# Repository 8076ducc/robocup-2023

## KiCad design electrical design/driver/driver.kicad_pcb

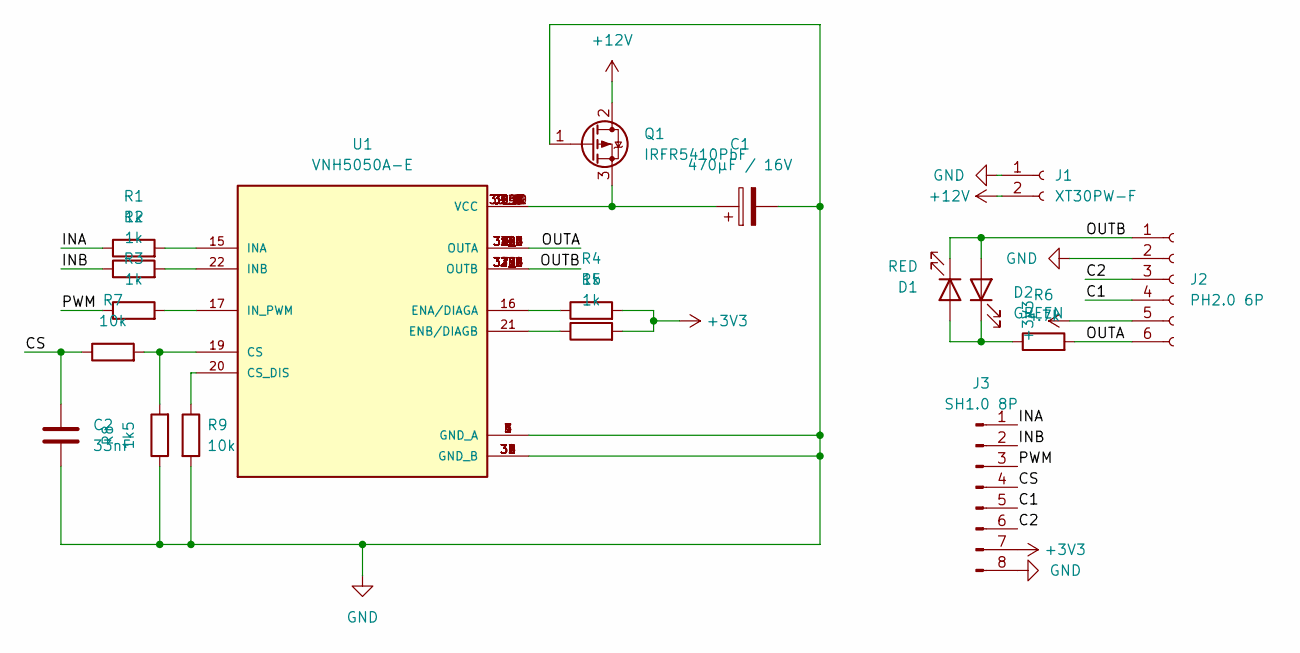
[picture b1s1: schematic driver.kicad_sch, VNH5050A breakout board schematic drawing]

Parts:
C1: 470µF / 16V; CP_Elec_8x10.5
C2: 33nF; C_0603_1608Metric
D1: RED; D_0603_1608Metric
D2: GREEN; D_0603_1608Metric
J1: XT30PW-F; AMASS_XT30PW-F_1x02_P2.50mm_Horizontal
J2: PH2.0 6P; JST_PH_S6B-PH-K_1x06_P2.00mm_Horizontal
J3: SH1.0 8P; JST_SH_BM08B-SRSS-TB_1x08-1MP_P1.00mm_Vertical
Q1: IRFR5410PbF; TO-252-2
R1, R2, R3, R4, R5: 1k; R_0603_1608Metric
R6: 4.7k; R_0603_1608Metric
R7, R9: 10k; R_0603_1608Metric
R8: 1k5; R_0603_1608Metric
U1: VNH5050A-E; SOP50P1030X247-39N; PARTREV 1.0

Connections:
+3V3: J2.5, J3.7, R4.2, R5.2
+12V: J1.2, Q1.2 (D)
/C1: J2.4, J3.5
/C2: J2.3, J3.6
/CS: C2.1, J3.4, R7.1
/INA: J3.1, R1.1
/INB: J3.2, R2.1
/OUTA: J2.6, R6.2, U1.2 (OUTA), U1.8 (OUTA), U1.9 (OUTA), U1.10 (OUTA), U1.11 (OUTA), U1.12 (OUTA), U1.14 (OUTA), U1.38 (OUTA), U1.38_1 (OUTA), U1.38_2 (OUTA), U1.38_3 (OUTA), U1.38_4 (OUTA), U1.38_5 (OUTA), U1.38_6 (OUTA)
/OUTB: D1.1 (K), D2.2 (A), J2.1, U1.23 (OUTB), U1.25 (OUTB), U1.26 (OUTB), U1.27 (OUTB), U1.28 (OUTB), U1.29 (OUTB), U1.35 (OUTB), U1.37 (OUTB), U1.37_1 (OUTB), U1.37_2 (OUTB), U1.37_3 (OUTB), U1.37_4 (OUTB), U1.37_5 (OUTB), U1.37_6 (OUTB)
/PWM: J3.3, R3.1
GND: C1.2, C2.2, J1.1, J2.2, J3.8, Q1.1 (G), R8.1, R9.2, U1.1 (GND_A), U1.3 (GND_A), U1.4 (GND_A), U1.5 (GND_A), U1.6 (GND_A), U1.7 (GND_A), U1.30 (GND_B), U1.31 (GND_B), U1.32 (GND_B), U1.33 (GND_B), U1.34 (GND_B), U1.36 (GND_B)
unnamed: C1.1, Q1.3 (S), U1.13 (VCC), U1.24 (VCC), U1.39 (VCC), U1.39_1 (VCC), U1.39_2 (VCC), U1.39_3 (VCC), U1.39_4 (VCC), U1.39_5 (VCC), U1.39_6 (VCC), U1.39_7 (VCC), U1.39_8 (VCC), U1.39_9 (VCC), U1.39_10 (VCC), U1.39_11 (VCC), U1.39_12 (VCC)
unnamed: D1.2 (A), D2.1 (K), R6.1
unnamed: R1.2, U1.15 (INA)
unnamed: R2.2, U1.22 (INB)
unnamed: R3.2, U1.17 (IN_PWM)
unnamed: R4.1, U1.16 (ENA/DIAGA)
unnamed: R5.1, U1.21 (ENB/DIAGB)
unnamed: R7.2, R8.2, U1.19 (CS)
unnamed: R9.1, U1.20 (CS_DIS)

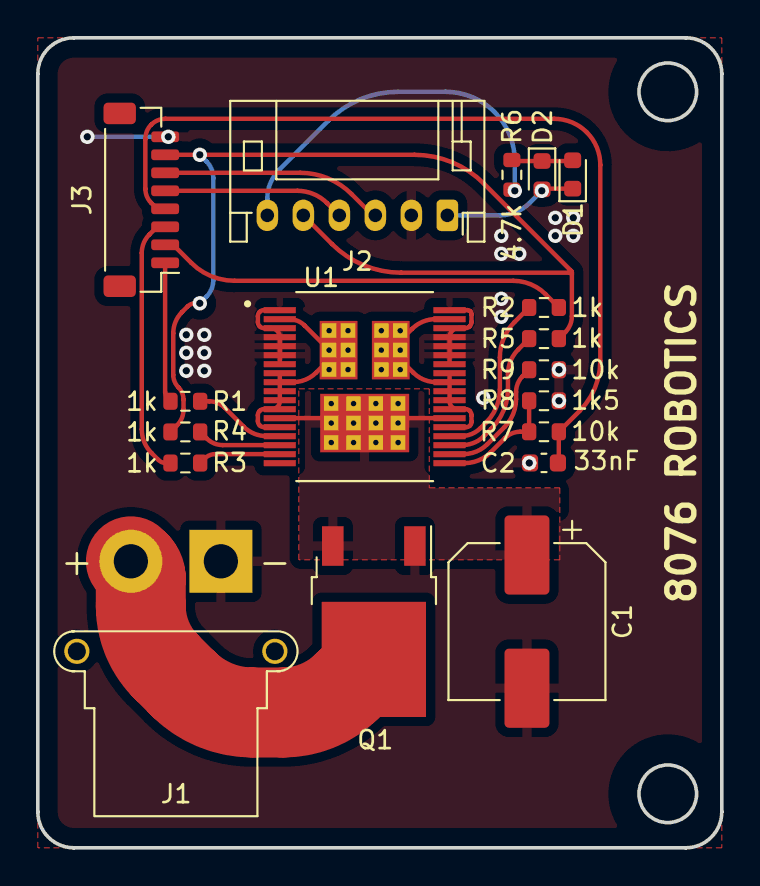
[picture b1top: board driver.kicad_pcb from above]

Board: 2 copper layers, 38.0 x 45.0 mm, 18 parts (0 on the bottom side), 20 nets.

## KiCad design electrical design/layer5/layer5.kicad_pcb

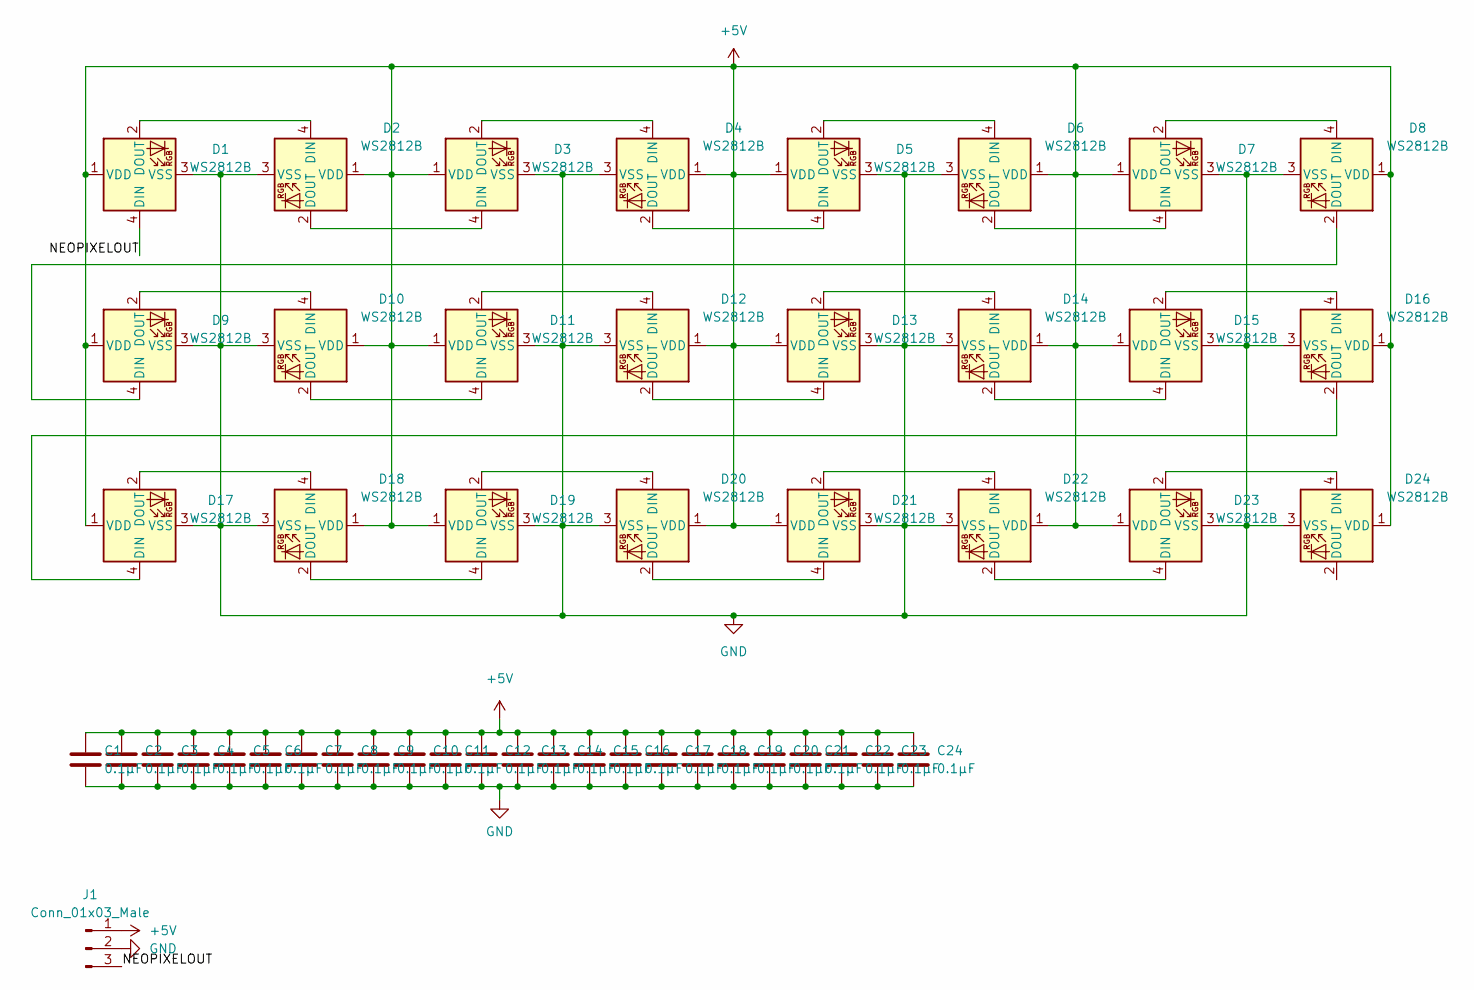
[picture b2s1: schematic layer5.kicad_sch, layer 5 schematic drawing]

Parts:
C1, C2, C3, C4, C5, C6, C7, C8, C9, C10, C11, C12, C13, C14, C15, C16, C17, C18, C19, C20, C21, C22, C23, C24: 0.1µF; C_0603_1608Metric
D1, D2, D3, D4, D5, D6, D7, D8, D9, D10, D11, D12, D13, D14, D15, D16, D17, D18, D19, D20, D21, D22, D23, D24: WS2812B; LED_WS2812B_PLCC4_5.0x5.0mm_P3.2mm
J1: Conn_01x03_Male; JST_SH_SM03B-SRSS-TB_1x03-1MP_P1.00mm_Horizontal

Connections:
+5V: C1.1, C2.1, C3.1, C4.1, C5.1, C6.1, C7.1, C8.1, C9.1, C10.1, C11.1, C12.1, C13.1, C14.1, C15.1, C16.1, C17.1, C18.1, C19.1, C20.1, C21.1, C22.1, C23.1, C24.1, D1.1 (VDD), D2.1 (VDD), D3.1 (VDD), D4.1 (VDD), D5.1 (VDD), D6.1 (VDD), D7.1 (VDD), D8.1 (VDD), D9.1 (VDD), D10.1 (VDD), D11.1 (VDD), D12.1 (VDD), D13.1 (VDD), D14.1 (VDD), D15.1 (VDD), D16.1 (VDD), D17.1 (VDD), D18.1 (VDD), D19.1 (VDD), D20.1 (VDD), D21.1 (VDD), D22.1 (VDD), D23.1 (VDD), D24.1 (VDD), J1.1
/NEOPIXELOUT: D1.4 (DIN), J1.3
GND: C1.2, C2.2, C3.2, C4.2, C5.2, C6.2, C7.2, C8.2, C9.2, C10.2, C11.2, C12.2, C13.2, C14.2, C15.2, C16.2, C17.2, C18.2, C19.2, C20.2, C21.2, C22.2, C23.2, C24.2, D1.3 (VSS), D2.3 (VSS), D3.3 (VSS), D4.3 (VSS), D5.3 (VSS), D6.3 (VSS), D7.3 (VSS), D8.3 (VSS), D9.3 (VSS), D10.3 (VSS), D11.3 (VSS), D12.3 (VSS), D13.3 (VSS), D14.3 (VSS), D15.3 (VSS), D16.3 (VSS), D17.3 (VSS), D18.3 (VSS), D19.3 (VSS), D20.3 (VSS), D21.3 (VSS), D22.3 (VSS), D23.3 (VSS), D24.3 (VSS), J1.2
unnamed: D1.2 (DOUT), D2.4 (DIN)
unnamed: D2.2 (DOUT), D3.4 (DIN)
unnamed: D3.2 (DOUT), D4.4 (DIN)
unnamed: D4.2 (DOUT), D5.4 (DIN)
unnamed: D5.2 (DOUT), D6.4 (DIN)
unnamed: D6.2 (DOUT), D7.4 (DIN)
unnamed: D7.2 (DOUT), D8.4 (DIN)
unnamed: D8.2 (DOUT), D9.4 (DIN)
unnamed: D10.2 (DOUT), D11.4 (DIN)
unnamed: D9.2 (DOUT), D10.4 (DIN)
unnamed: D11.2 (DOUT), D12.4 (DIN)
unnamed: D12.2 (DOUT), D13.4 (DIN)
unnamed: D13.2 (DOUT), D14.4 (DIN)
unnamed: D14.2 (DOUT), D15.4 (DIN)
unnamed: D15.2 (DOUT), D16.4 (DIN)
unnamed: D16.2 (DOUT), D17.4 (DIN)
unnamed: D17.2 (DOUT), D18.4 (DIN)
unnamed: D18.2 (DOUT), D19.4 (DIN)
unnamed: D19.2 (DOUT), D20.4 (DIN)
unnamed: D20.2 (DOUT), D21.4 (DIN)
unnamed: D21.2 (DOUT), D22.4 (DIN)
unnamed: D22.2 (DOUT), D23.4 (DIN)
unnamed: D23.2 (DOUT), D24.4 (DIN)

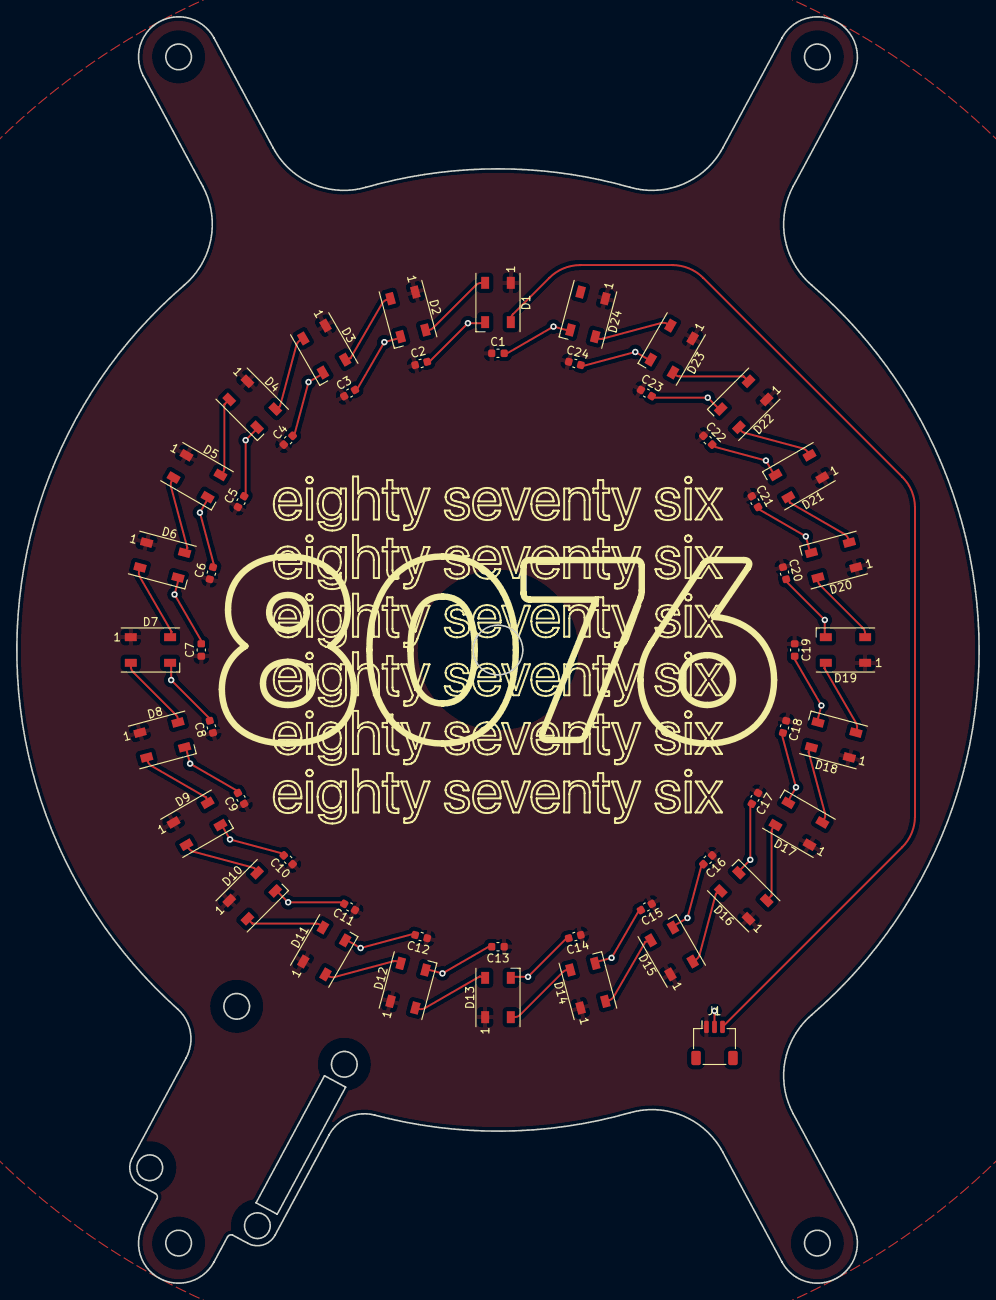
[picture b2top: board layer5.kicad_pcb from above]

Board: 2 copper layers, 120.0 x 157.9 mm, 49 parts (0 on the bottom side), 26 nets.

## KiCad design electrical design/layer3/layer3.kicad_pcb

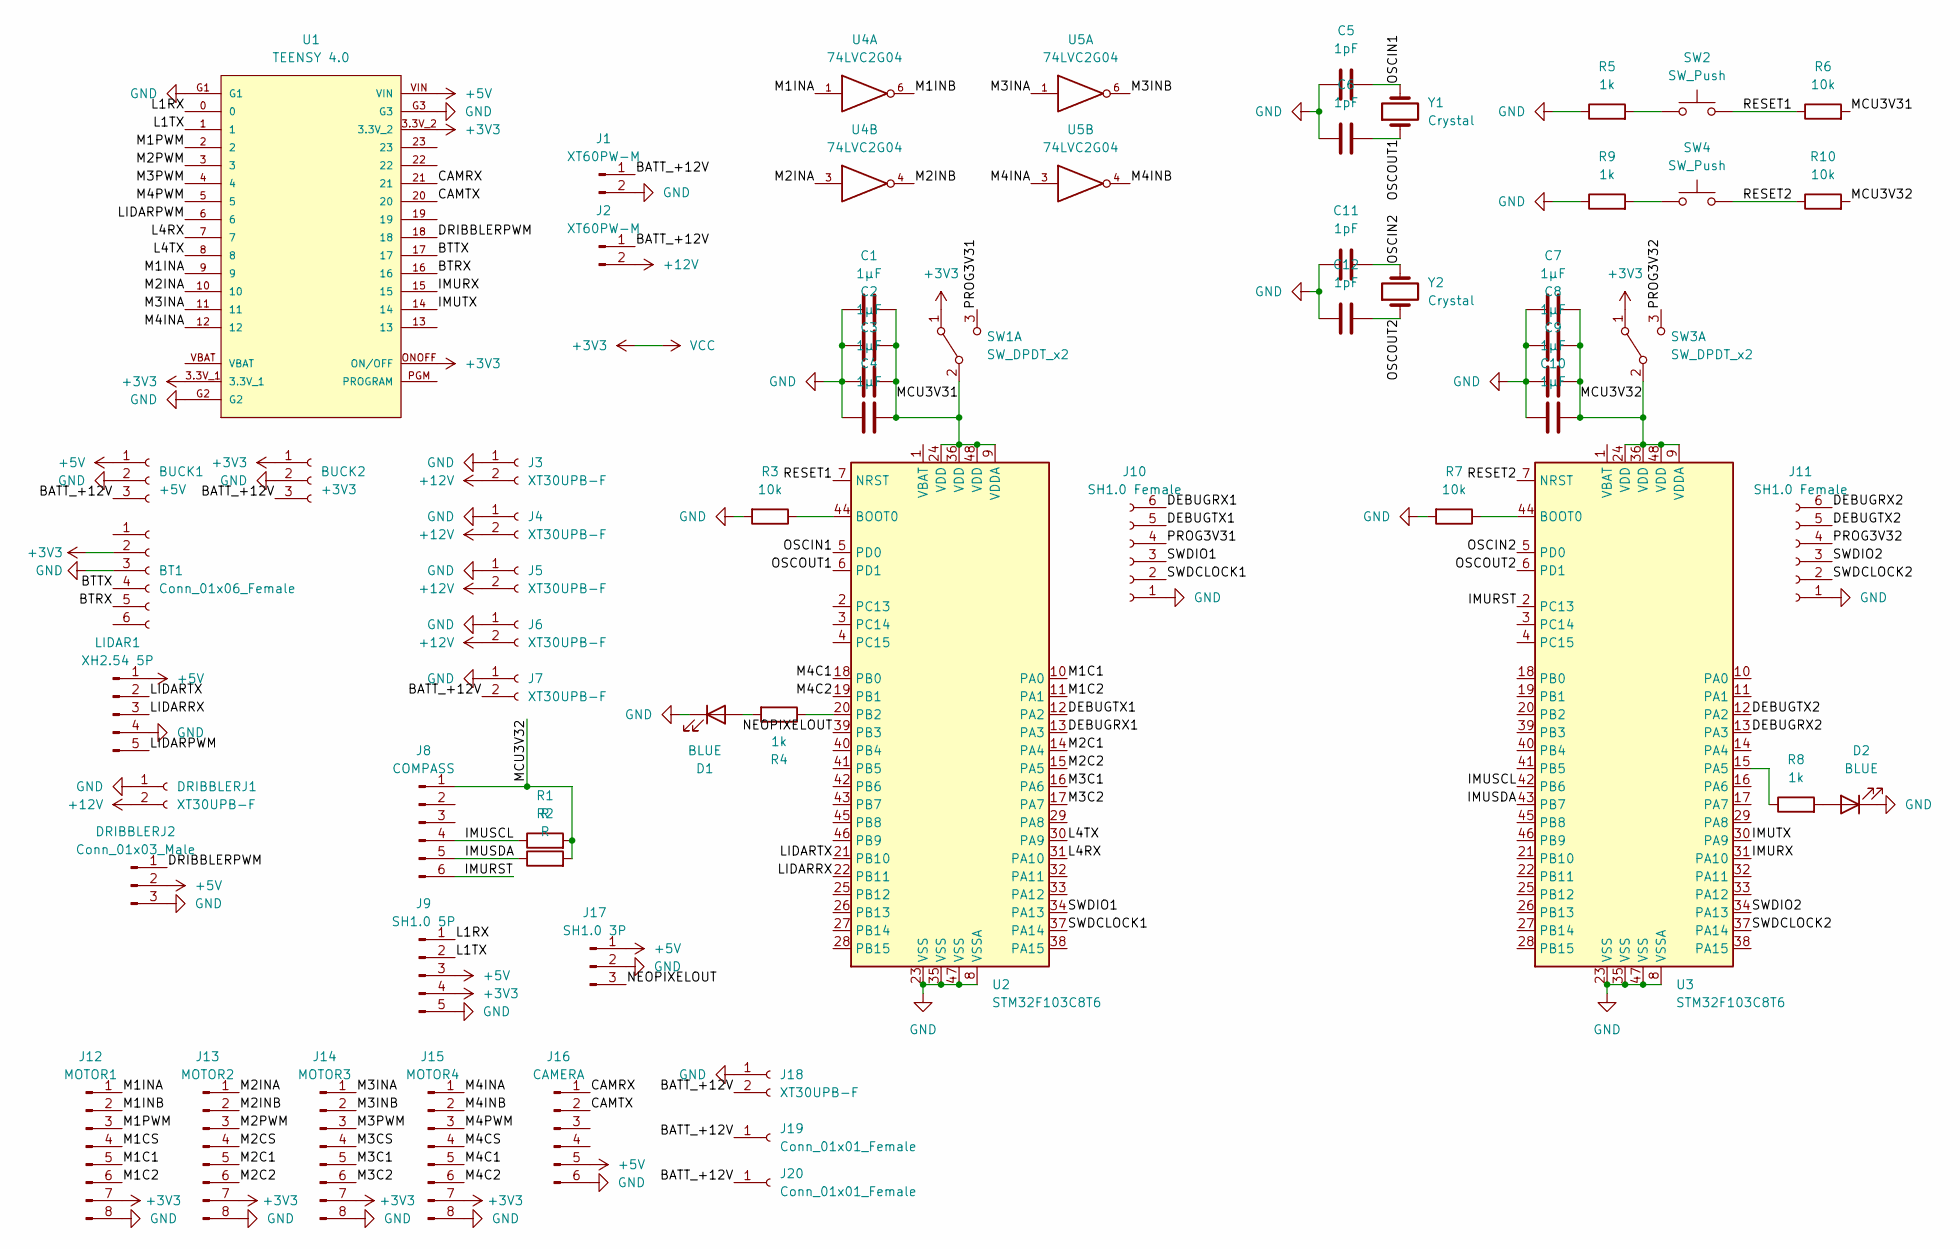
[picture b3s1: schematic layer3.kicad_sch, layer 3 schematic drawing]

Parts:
BT1: Conn_01x06_Female; PinSocket_1x06_P2.54mm_Horizontal
BUCK1: +5V; PinHeader_1x03_P2.54mm_Vertical
BUCK2: +3V3; PinHeader_1x03_P2.54mm_Vertical
C1, C2, C3, C4, C7, C8, C9, C10: 1μF; C_0603_1608Metric
C5, C6, C11, C12: 1pF; C_0603_1608Metric
D1, D2: BLUE; D_0603_1608Metric
DRIBBLERJ1: XT30UPB-F; AMASS_XT30UPB-F_1x02_P5.0mm_Vertical
DRIBBLERJ2: Conn_01x03_Male; PinHeader_1x03_P2.54mm_Vertical
J1, J2: XT60PW-M; AMASS_XT60PW-M
J3, J4, J5, J6, J7, J18: XT30UPB-F; AMASS_XT30UPB-F_1x02_P5.0mm_Vertical
J8: COMPASS; PinHeader_1x06_P2.54mm_Vertical
J9: SH1.0 5P; JST_SH_BM05B-SRSS-TB_1x05-1MP_P1.00mm_Vertical
J10, J11: SH1.0 Female; JST_SH_BM06B-SRSS-TB_1x06-1MP_P1.00mm_Vertical
J12: MOTOR1; JST_SH_BM08B-SRSS-TB_1x08-1MP_P1.00mm_Vertical
J13: MOTOR2; JST_SH_BM08B-SRSS-TB_1x08-1MP_P1.00mm_Vertical
J14: MOTOR3; JST_SH_BM08B-SRSS-TB_1x08-1MP_P1.00mm_Vertical
J15: MOTOR4; JST_SH_BM08B-SRSS-TB_1x08-1MP_P1.00mm_Vertical
J16: CAMERA; JST_GH_SM06B-GHS-TB_1x06-1MP_P1.25mm_Horizontal
J17: SH1.0 3P; JST_SH_BM03B-SRSS-TB_1x03-1MP_P1.00mm_Vertical
J19, J20: Conn_01x01_Female; SolderWire-1.5sqmm_1x01_D1.7mm_OD3.9mm
LIDAR1: XH2.54 5P; JST_XH_B5B-XH-A_1x05_P2.50mm_Vertical
R1, R2: R; R_0603_1608Metric
R3, R6, R7, R10: 10k; R_0603_1608Metric
R4, R5, R8, R9: 1k; R_0603_1608Metric
SW1, SW3: SW_DPDT_x2; SWITCH_SPDT_PTH_11.6X4.0MM_LOCK
SW2, SW4: SW_Push; SW_Push_SPST_NO_Alps_SKRK
U1: TEENSY 4.0; Teensy40
U2, U3: STM32F103C8T6; LQFP-48_7x7mm_P0.5mm
U4, U5: 74LVC2G04; SOT-23-6
Y1, Y2: Crystal; Crystal_SMD_5032-2Pin_5.0x3.2mm

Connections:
+3V3: BT1.2, BUCK2.1, J9.4, J12.7, J13.7, J14.7, J15.7, SW1.1 (A), SW3.1 (A), U1.3.3V_1, U1.3.3V_2, U1.ONOFF (ON/OFF), U4.5 (VCC), U5.5 (VCC)
+5V: BUCK1.1, DRIBBLERJ2.2, J9.3, J16.5, J17.1, LIDAR1.1, U1.VIN
+12V: DRIBBLERJ1.2, J2.2, J3.2, J4.2, J5.2, J6.2
/BATT_+12V: BUCK1.3, BUCK2.3, J1.1, J2.1, J7.2, J18.2, J19.1, J20.1
/BTRX: BT1.5, U1.16
/BTTX: BT1.4, U1.17
/CAMRX: J16.1, U1.21
/CAMTX: J16.2, U1.20
/DEBUGRX1: J10.6, U2.13 (PA3)
/DEBUGRX2: J11.6, U3.13 (PA3)
/DEBUGTX1: J10.5, U2.12 (PA2)
/DEBUGTX2: J11.5, U3.12 (PA2)
/DRIBBLERPWM: DRIBBLERJ2.1, U1.18
/IMURST: J8.6, U3.2 (PC13)
/IMURX: U1.15, U3.31 (PA10)
/IMUSCL: J8.4, R1.1, U3.42 (PB6)
/IMUSDA: J8.5, R2.1, U3.43 (PB7)
/IMUTX: U1.14, U3.30 (PA9)
/L1RX: J9.1, U1.0
/L1TX: J9.2, U1.1
/L4RX: U1.7, U2.31 (PA10)
/L4TX: U1.8, U2.30 (PA9)
/LIDARPWM: LIDAR1.5, U1.6
/LIDARRX: LIDAR1.3, U2.22 (PB11)
/LIDARTX: LIDAR1.2, U2.21 (PB10)
/M1C1: J12.5, U2.10 (PA0)
/M1C2: J12.6, U2.11 (PA1)
/M1CS: J12.4
/M1INA: J12.1, U1.9, U4.1
/M1INB: J12.2, U4.6
/M1PWM: J12.3, U1.2
/M2C1: J13.5, U2.14 (PA4)
/M2C2: J13.6, U2.15 (PA5)
/M2CS: J13.4
/M2INA: J13.1, U1.10, U4.3
/M2INB: J13.2, U4.4
/M2PWM: J13.3, U1.3
/M3C1: J14.5, U2.16 (PA6)
/M3C2: J14.6, U2.17 (PA7)
/M3CS: J14.4
/M3INA: J14.1, U1.11, U5.1
/M3INB: J14.2, U5.6
/M3PWM: J14.3, U1.4
/M4C1: J15.5, U2.18 (PB0)
/M4C2: J15.6, U2.19 (PB1)
/M4CS: J15.4
/M4INA: J15.1, U1.12, U5.3
/M4INB: J15.2, U5.4
/M4PWM: J15.3, U1.5
/MCU3V31: C1.2, C2.2, C3.2, C4.2, R6.2, SW1.2 (B), U2.9 (VDDA), U2.24 (VDD), U2.36 (VDD), U2.48 (VDD)
/MCU3V32: C7.2, C8.2, C9.2, C10.2, J8.1, R1.2, R2.2, R10.2, SW3.2 (B), U3.9 (VDDA), U3.24 (VDD), U3.36 (VDD), U3.48 (VDD)
/NEOPIXELOUT: J17.3, U2.39 (PB3)
/OSCIN1: C5.2, U2.5 (PD0), Y1.2
/OSCIN2: C11.2, U3.5 (PD0), Y2.2
/OSCOUT1: C6.2, U2.6 (PD1), Y1.1
/OSCOUT2: C12.2, U3.6 (PD1), Y2.1
/PROG3V31: J10.4, SW1.3 (C)
/PROG3V32: J11.4, SW3.3 (C)
/RESET1: R6.1, SW2.2, U2.7 (NRST)
/RESET2: R10.1, SW4.2, U3.7 (NRST)
/SWDCLOCK1: J10.2, U2.37 (PA14)
/SWDCLOCK2: J11.2, U3.37 (PA14)
/SWDIO1: J10.3, U2.34 (PA13)
/SWDIO2: J11.3, U3.34 (PA13)
GND: BT1.3, BUCK1.2, BUCK2.2, C1.1, C2.1, C3.1, C4.1, C5.1, C6.1, C7.1, C8.1, C9.1, C10.1, C11.1, C12.1, D1.1 (K), D2.1 (K), DRIBBLERJ1.1, DRIBBLERJ2.3, J1.2, J3.1, J4.1, J5.1, J6.1, J7.1, J9.5, J10.1, J11.1, J12.8, J13.8, J14.8, J15.8, J16.6, J17.2, J18.1, LIDAR1.4, R3.2, R5.1, R7.2, R9.1, U1.G1, U1.G2, U1.G3, U2.8 (VSSA), U2.23 (VSS), U2.35 (VSS), U2.47 (VSS), U3.8 (VSSA), U3.23 (VSS), U3.35 (VSS), U3.47 (VSS), U4.2 (GND), U5.2 (GND)
unnamed: D1.2 (A), R4.2
unnamed: D2.2 (A), R8.2
unnamed: R3.1, U2.44 (BOOT0)
unnamed: R4.1, U2.20 (PB2)
unnamed: R5.2, SW2.1
unnamed: R7.1, U3.44 (BOOT0)
unnamed: R8.1, U3.15 (PA5)
unnamed: R9.2, SW4.1

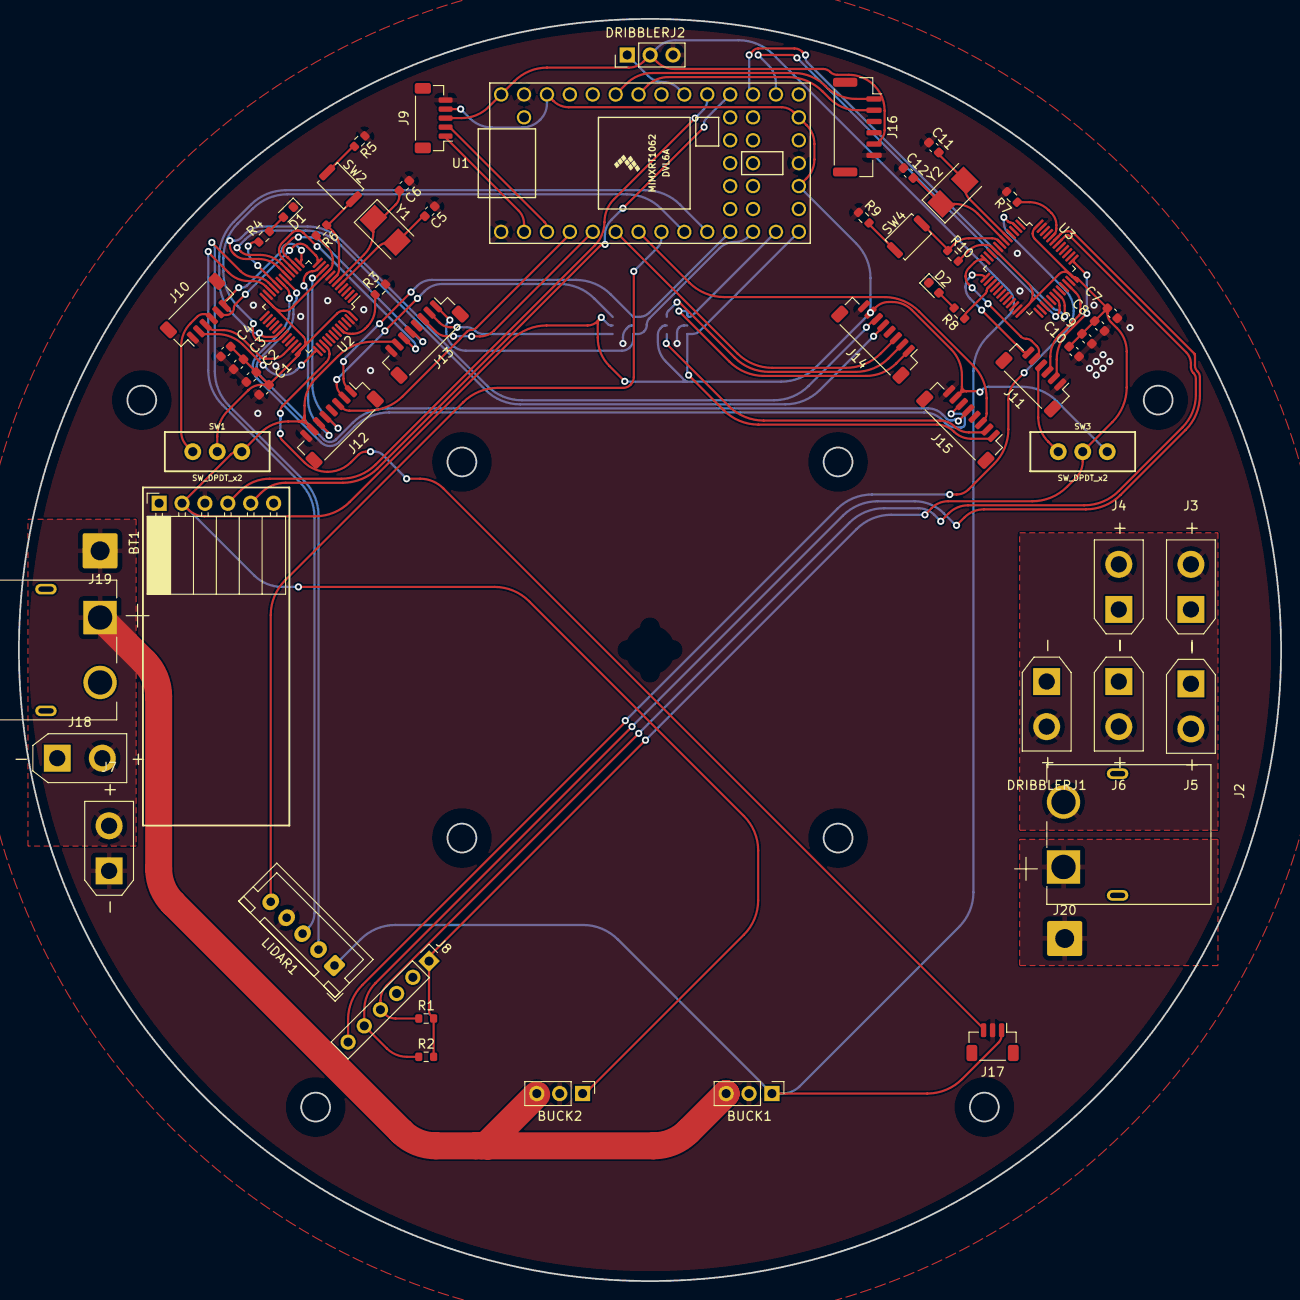
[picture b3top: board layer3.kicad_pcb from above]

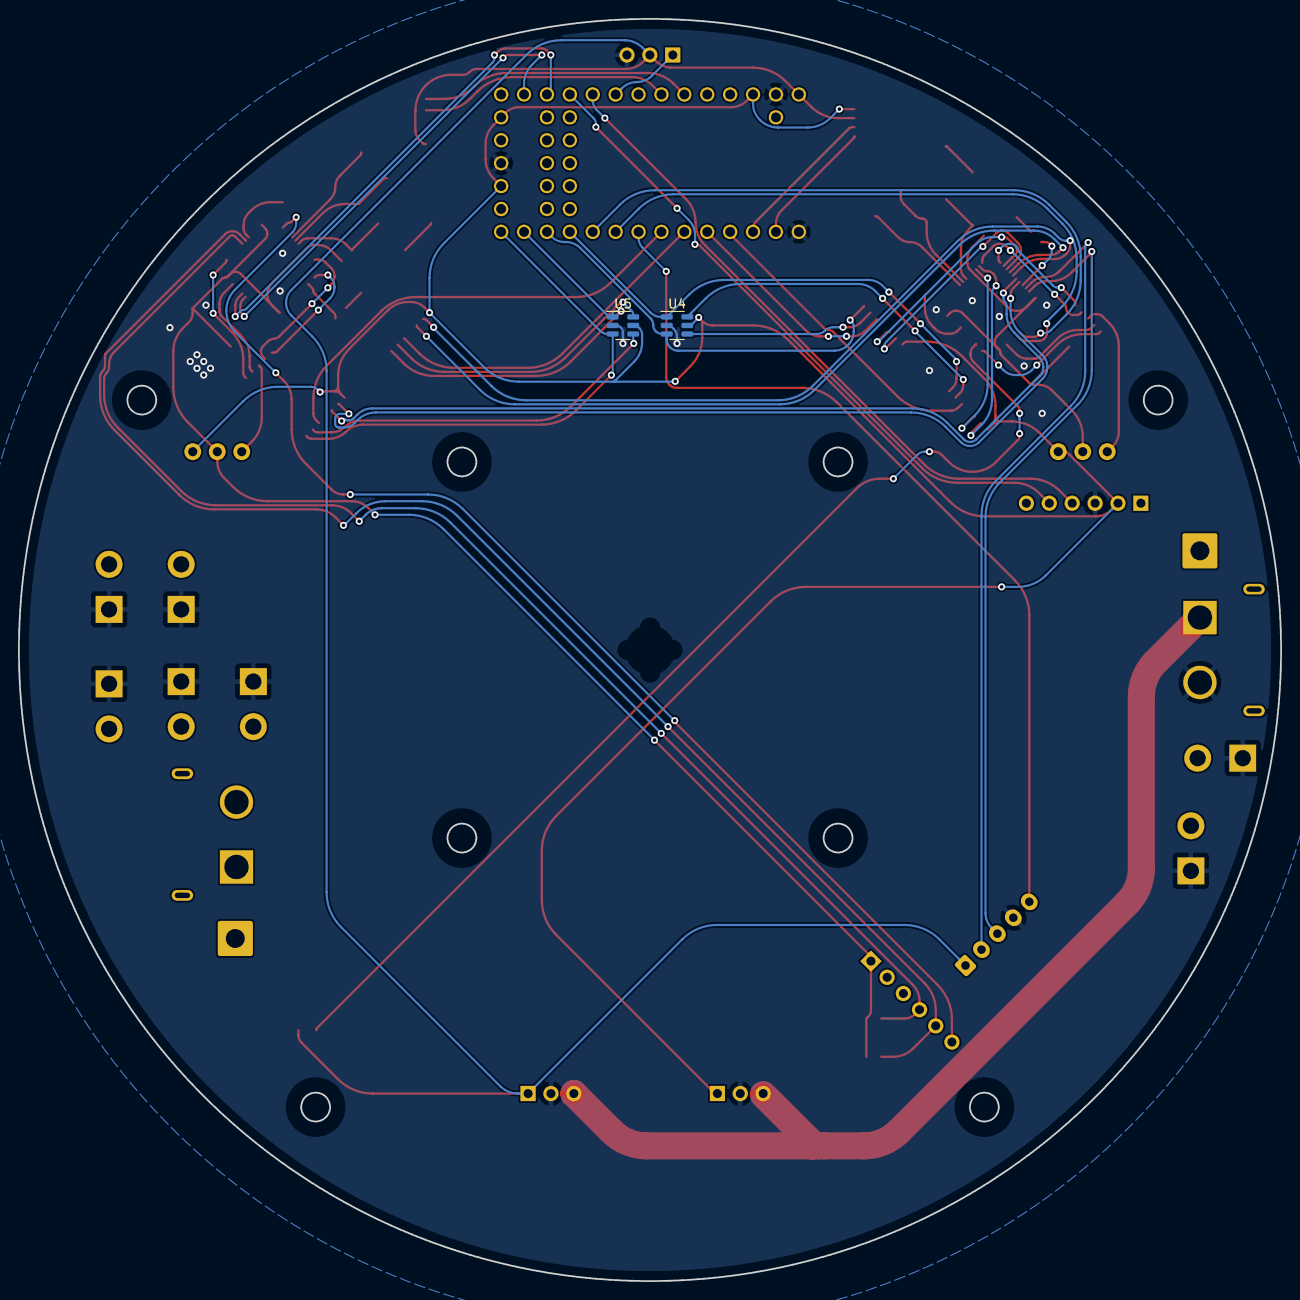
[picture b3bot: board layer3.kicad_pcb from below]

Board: 2 copper layers, 140.0 x 140.0 mm, 61 parts (2 on the bottom side), 69 nets.

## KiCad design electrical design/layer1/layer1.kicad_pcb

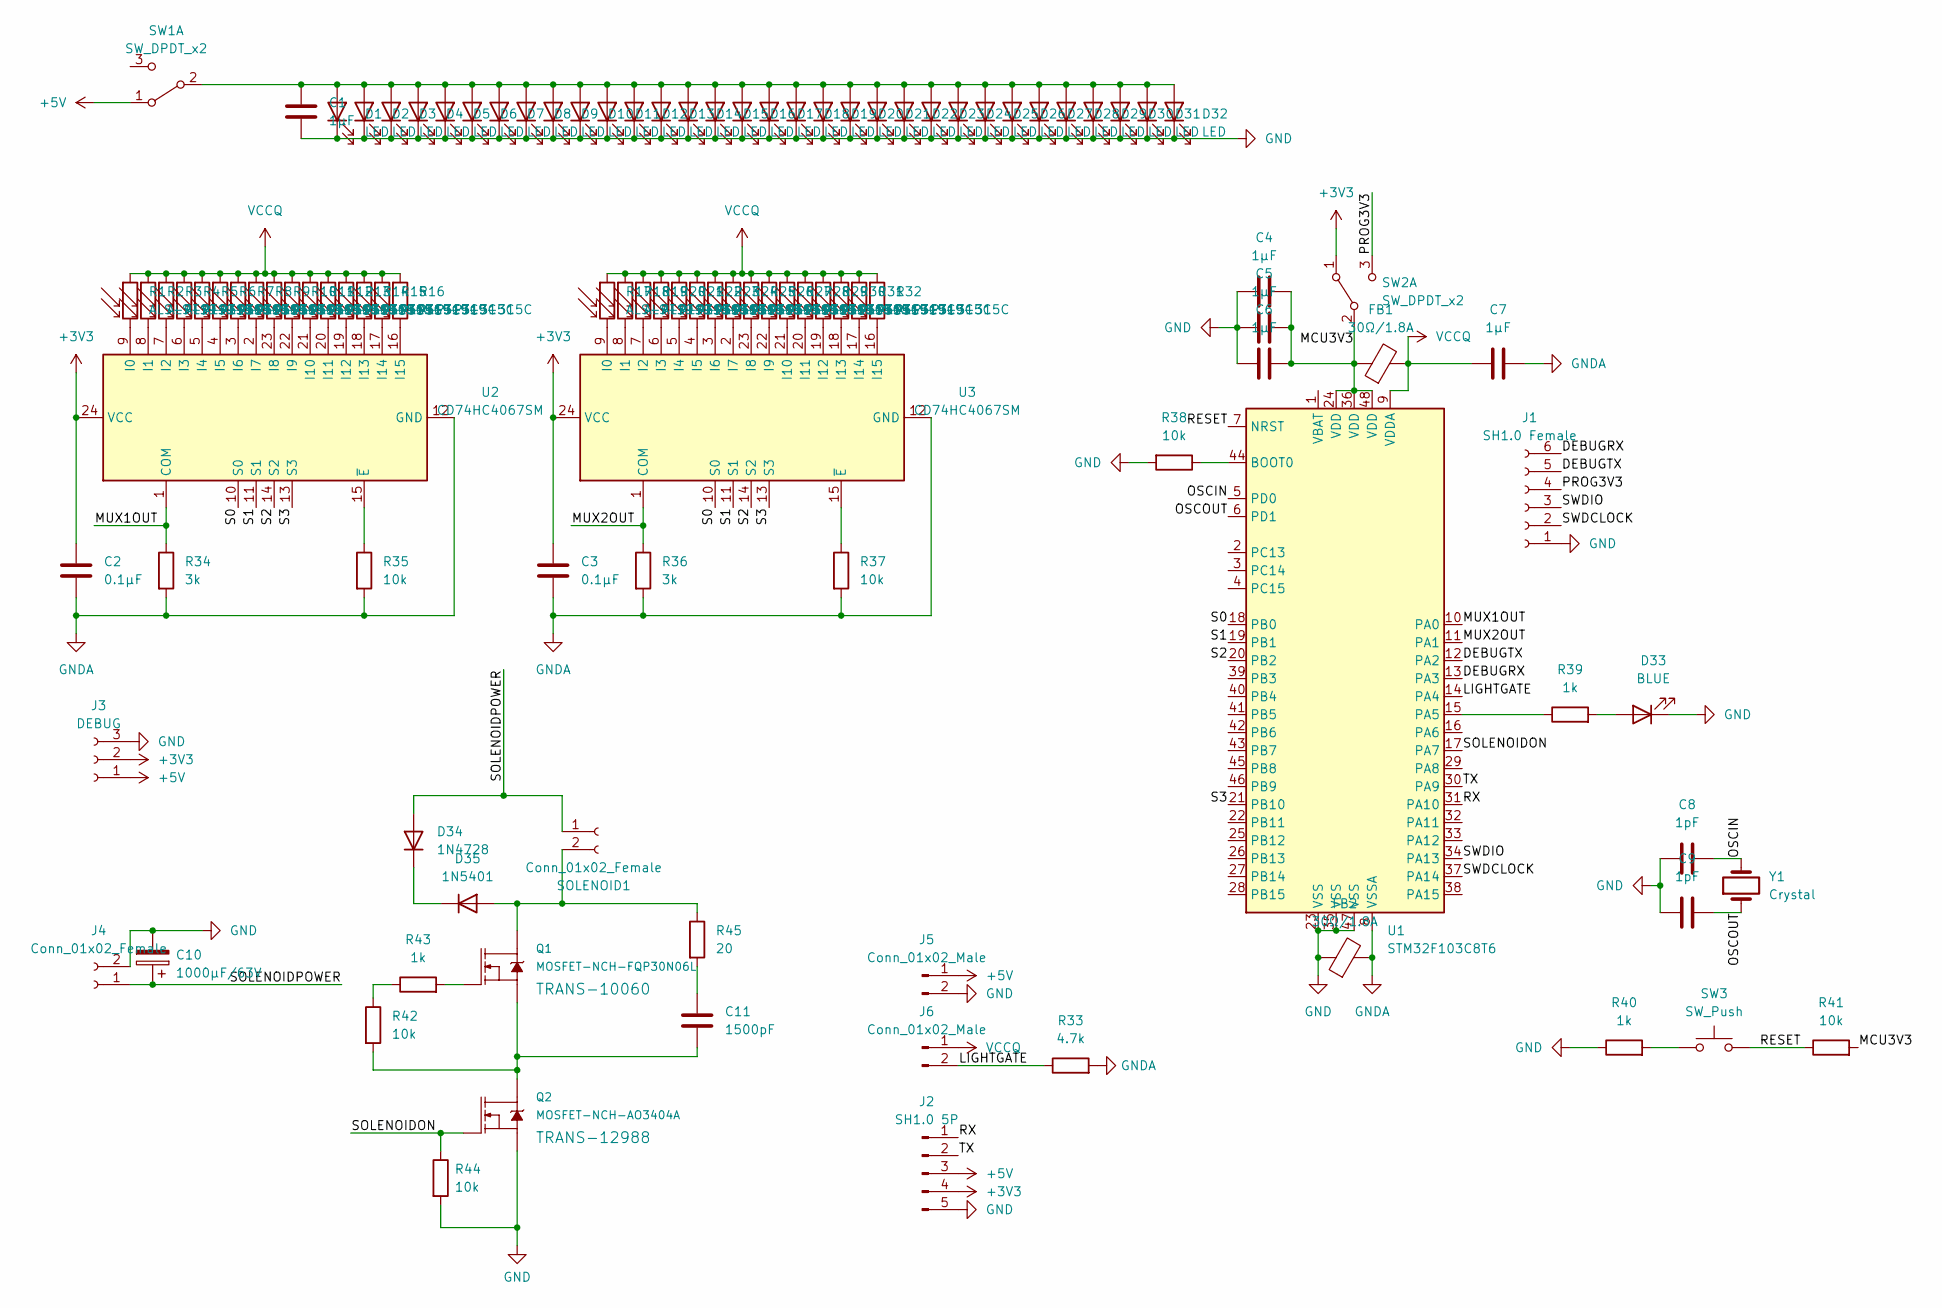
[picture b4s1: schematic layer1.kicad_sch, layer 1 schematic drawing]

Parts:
C1, C4, C5, C6, C7: 1μF; C_0603_1608Metric
C2, C3: 0.1μF; C_0603_1608Metric
C8, C9: 1pF; C_0603_1608Metric
C10: 1000µF/63V; CP_Radial_D16.0mm_P7.50mm
C11: 1500pF; C_0603_1608Metric
D1, D2, D3, D4, D5, D6, D7, D8, D9, D10, D11, D12, D13, D14, D15, D16, D17, D18, D19, D20, D21, D22, D23, D24, D25, D26, D27, D28, D29, D30, D31, D32: LED; CP_EIA-3528-12_Kemet-T
D33: BLUE; D_0603_1608Metric
D34: 1N4728; D_DO-41_SOD81_P10.16mm_Horizontal
D35: 1N5401; D_DO-27_P15.24mm_Horizontal
FB1, FB2: 30Ω/1.8A; C_0603_1608Metric
J1: SH1.0 Female; JST_SH_BM06B-SRSS-TB_1x06-1MP_P1.00mm_Vertical
J2: SH1.0 5P; JST_SH_BM05B-SRSS-TB_1x05-1MP_P1.00mm_Vertical
J3: DEBUG; PinHeader_1x03_P2.54mm_Vertical
J4: Conn_01x02_Female; AMASS_XT30UPB-F_1x02_P5.0mm_Vertical
J5, J6: Conn_01x02_Male; PinHeader_1x02_P2.54mm_Vertical
Q1: MOSFET-NCH-FQP30N06L; TO-220-3_Vertical
Q2: MOSFET-NCH-AO3404A; TSOT-23
R1, R2, R3, R4, R5, R6, R7, R8, R9, R10, R11, R12, R13, R14, R15, R16, R17, R18, R19, R20, R21, R22, R23, R24, R25, R26, R27, R28, R29, R30, R31, R32: ALS-PT19-315C; R_0603_1608Metric
R33: 4.7k; R_0603_1608Metric
R34, R36: 3k; R_0603_1608Metric
R35, R37, R38, R41, R42, R44: 10k; R_0603_1608Metric
R39, R40, R43: 1k; R_0603_1608Metric
R45: 20; R_0603_1608Metric
SOLENOID1: Conn_01x02_Female; AMASS_XT30UPB-F_1x02_P5.0mm_Vertical
SW1, SW2: SW_DPDT_x2; SWITCH_SPDT_PTH_11.6X4.0MM_LOCK
SW3: SW_Push; SW_Push_SPST_NO_Alps_SKRK
U1: STM32F103C8T6; LQFP-48_7x7mm_P0.5mm
U2, U3: CD74HC4067SM; SSOP-24_5.3x8.2mm_P0.65mm
Y1: Crystal; Crystal_SMD_5032-2Pin_5.0x3.2mm

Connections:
+3V3: C2.1, C3.1, J2.4, J3.2, SW2.1 (A), U2.24 (VCC), U3.24 (VCC)
+5V: J2.3, J3.1, J5.1, SW1.1 (A)
/DEBUGRX: J1.6, U1.13 (PA3)
/DEBUGTX: J1.5, U1.12 (PA2)
/LIGHTGATE: J6.2, R33.1, U1.14 (PA4)
/MCU3V3: C4.2, C5.2, C6.2, FB1.1, R41.2, SW2.2 (B), U1.24 (VDD), U1.36 (VDD), U1.48 (VDD)
/MUX1OUT: R34.1, U1.10 (PA0), U2.1 (COM)
/MUX2OUT: R36.1, U1.11 (PA1), U3.1 (COM)
/OSCIN: C8.2, U1.5 (PD0), Y1.2
/OSCOUT: C9.2, U1.6 (PD1), Y1.1
/PROG3V3: J1.4, SW2.3 (C)
/RESET: R41.1, SW3.2, U1.7 (NRST)
/RX: J2.1, U1.31 (PA10)
/S0: U1.18 (PB0), U2.10 (S0), U3.10 (S0)
/S1: U1.19 (PB1), U2.11 (S1), U3.11 (S1)
/S2: U1.20 (PB2), U2.14 (S2), U3.14 (S2)
/S3: U1.21 (PB10), U2.13 (S3), U3.13 (S3)
/SOLENOIDON: Q2.1 (G), R44.1, U1.17 (PA7)
/SOLENOIDPOWER: C10.1, D34.2 (A), J4.1, SOLENOID1.1
/SWDCLOCK: J1.2, U1.37 (PA14)
/SWDIO: J1.3, U1.34 (PA13)
/TX: J2.2, U1.30 (PA9)
GND: C1.2, C4.1, C5.1, C6.1, C8.1, C9.1, C10.2, D1.1 (K), D2.1 (K), D3.1 (K), D4.1 (K), D5.1 (K), D6.1 (K), D7.1 (K), D8.1 (K), D9.1 (K), D10.1 (K), D11.1 (K), D12.1 (K), D13.1 (K), D14.1 (K), D15.1 (K), D16.1 (K), D17.1 (K), D18.1 (K), D19.1 (K), D20.1 (K), D21.1 (K), D22.1 (K), D23.1 (K), D24.1 (K), D25.1 (K), D26.1 (K), D27.1 (K), D28.1 (K), D29.1 (K), D30.1 (K), D31.1 (K), D32.1 (K), D33.1 (K), FB2.1, J1.1, J2.5, J3.3, J4.2, J5.2, Q2.2 (S), R38.2, R40.1, R44.2, U1.23 (VSS), U1.35 (VSS), U1.47 (VSS)
unnamed: C1.1, D1.2 (A), D2.2 (A), D3.2 (A), D4.2 (A), D5.2 (A), D6.2 (A), D7.2 (A), D8.2 (A), D9.2 (A), D10.2 (A), D11.2 (A), D12.2 (A), D13.2 (A), D14.2 (A), D15.2 (A), D16.2 (A), D17.2 (A), D18.2 (A), D19.2 (A), D20.2 (A), D21.2 (A), D22.2 (A), D23.2 (A), D24.2 (A), D25.2 (A), D26.2 (A), D27.2 (A), D28.2 (A), D29.2 (A), D30.2 (A), D31.2 (A), D32.2 (A), SW1.2 (B)
unnamed: C11.1, R45.2
unnamed: C11.2, Q1.3 (S), Q2.3 (D), R42.2
unnamed: D33.2 (A), R39.2
unnamed: D34.1 (K), D35.1 (K)
unnamed: D35.2 (A), Q1.2 (D), R45.1, SOLENOID1.2
unnamed: Q1.1 (G), R43.2
unnamed: R1.2, U2.9 (I0)
unnamed: R2.2, U2.8 (I1)
unnamed: R3.2, U2.7 (I2)
unnamed: R4.2, U2.6 (I3)
unnamed: R5.2, U2.5 (I4)
unnamed: R6.2, U2.4 (I5)
unnamed: R7.2, U2.3 (I6)
unnamed: R8.2, U2.2 (I7)
unnamed: R9.2, U2.23 (I8)
unnamed: R10.2, U2.22 (I9)
unnamed: R11.2, U2.21 (I10)
unnamed: R12.2, U2.20 (I11)
unnamed: R13.2, U2.19 (I12)
unnamed: R14.2, U2.18 (I13)
unnamed: R15.2, U2.17 (I14)
unnamed: R16.2, U2.16 (I15)
unnamed: R17.2, U3.9 (I0)
unnamed: R18.2, U3.8 (I1)
unnamed: R19.2, U3.7 (I2)
unnamed: R20.2, U3.6 (I3)
unnamed: R21.2, U3.5 (I4)
unnamed: R22.2, U3.4 (I5)
unnamed: R23.2, U3.3 (I6)
unnamed: R24.2, U3.2 (I7)
unnamed: R25.2, U3.23 (I8)
unnamed: R26.2, U3.22 (I9)
unnamed: R27.2, U3.21 (I10)
unnamed: R28.2, U3.20 (I11)
unnamed: R29.2, U3.19 (I12)
unnamed: R30.2, U3.18 (I13)
unnamed: R31.2, U3.17 (I14)
unnamed: R32.2, U3.16 (I15)
unnamed: R35.1, U2.15 (~E)
unnamed: R37.1, U3.15 (~E)
unnamed: R38.1, U1.44 (BOOT0)
unnamed: R39.1, U1.15 (PA5)
unnamed: R40.2, SW3.1
unnamed: R42.1, R43.1
VCCQ: C7.1, FB1.2, J6.1, R1.1, R2.1, R3.1, R4.1, R5.1, R6.1, R7.1, R8.1, R9.1, R10.1, R11.1, R12.1, R13.1, R14.1, R15.1, R16.1, R17.1, R18.1, R19.1, R20.1, R21.1, R22.1, R23.1, R24.1, R25.1, R26.1, R27.1, R28.1, R29.1, R30.1, R31.1, R32.1, U1.9 (VDDA)

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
